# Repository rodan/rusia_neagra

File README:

power supply assy redesign for the Rusia Neagra MKII amplifier made by VIOTUBEAMP

https://www.tehnium-azi.ro/forums/topic/6689-proiectul-nr49-amplificatorul-rusia-neagra/?tab=comments#comment-73357

pictures of the build are available here:
https://photos.app.goo.gl/SxAB8hwyef6rpiTH7

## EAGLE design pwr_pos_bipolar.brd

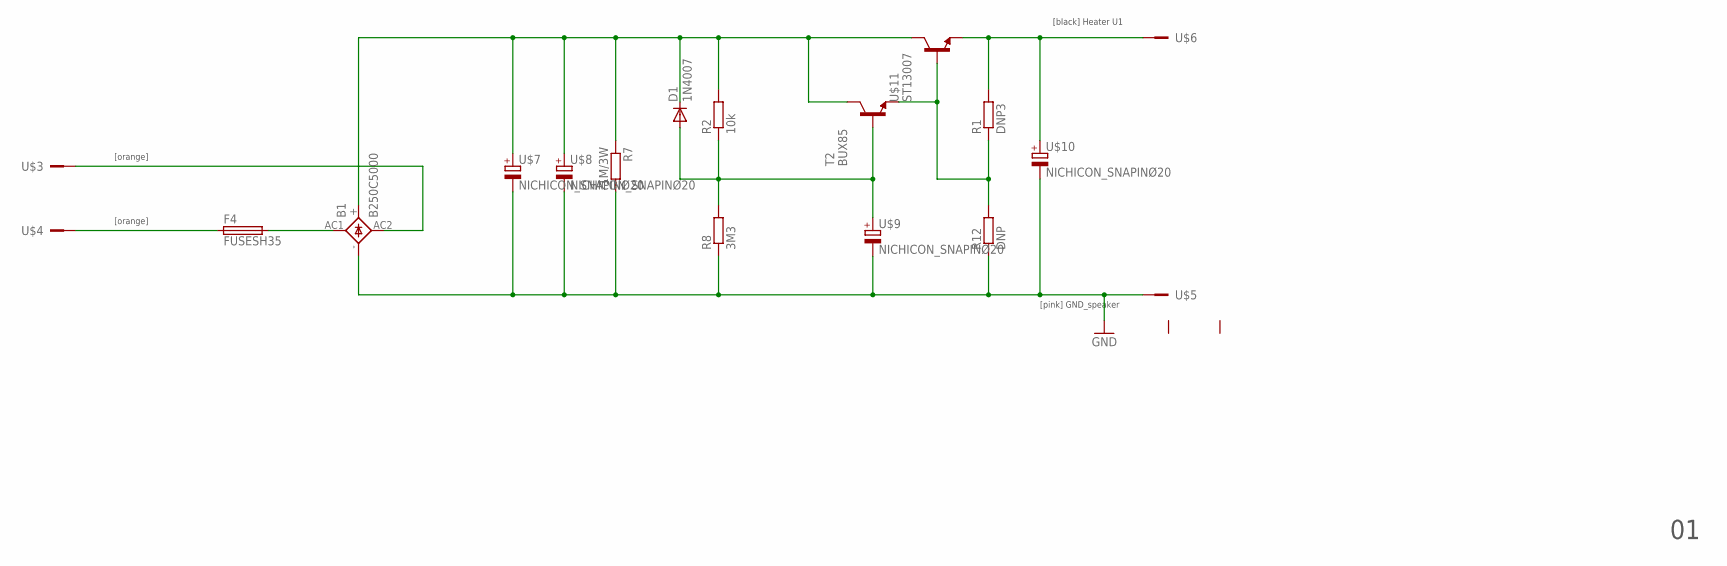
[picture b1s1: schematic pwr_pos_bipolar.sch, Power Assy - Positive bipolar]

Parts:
B1: B250C5000; DIOTEC_BC5000
D1: 1N4007; DO41-10
F4: FUSESH35; SH25
R1: DNP3; 0411/12
R2: 10k; 0411/12
R7: 1M/3W; 0922V
R8: 3M3; 0411/12
R12: DNP; 0411/12
T2: BUX85; TO220V
U$1: SK456-60-3XM3L
U$2: RN_POWER; RN
U$3, U$4, U$5, U$6: M1; M1_OFFSET
U$7, U$8, U$9, U$10: NICHICON_SNAPINØ20; C_20G10
U$11: ST13007; TOP3V_TO220

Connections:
30VAC_1: B1.AC2, U$3.1
30VAC_2: F4.1, U$4.1
GND: B1.-, R7.2, R8.1, R12.1, U$5.1, U$7.-, U$8.-, U$9.-, U$10.-
unnamed: B1.AC1, F4.2
unnamed: R1.1, R12.2, T2.3 (E), U$11.B, U$11.B$1 (B)
unnamed: D1.A, R2.1, R8.2, T2.1 (B), U$9.+
N_C: B1.+, D1.C, R2.2, R7.1, T2.2 (C), U$7.+, U$8.+, U$11.C
V-: R1.2, U$6.1, U$10.+, U$11.E, U$11.E$1 (E)

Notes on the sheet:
[orange]
[pink] GND_speaker
[black] Heater U1

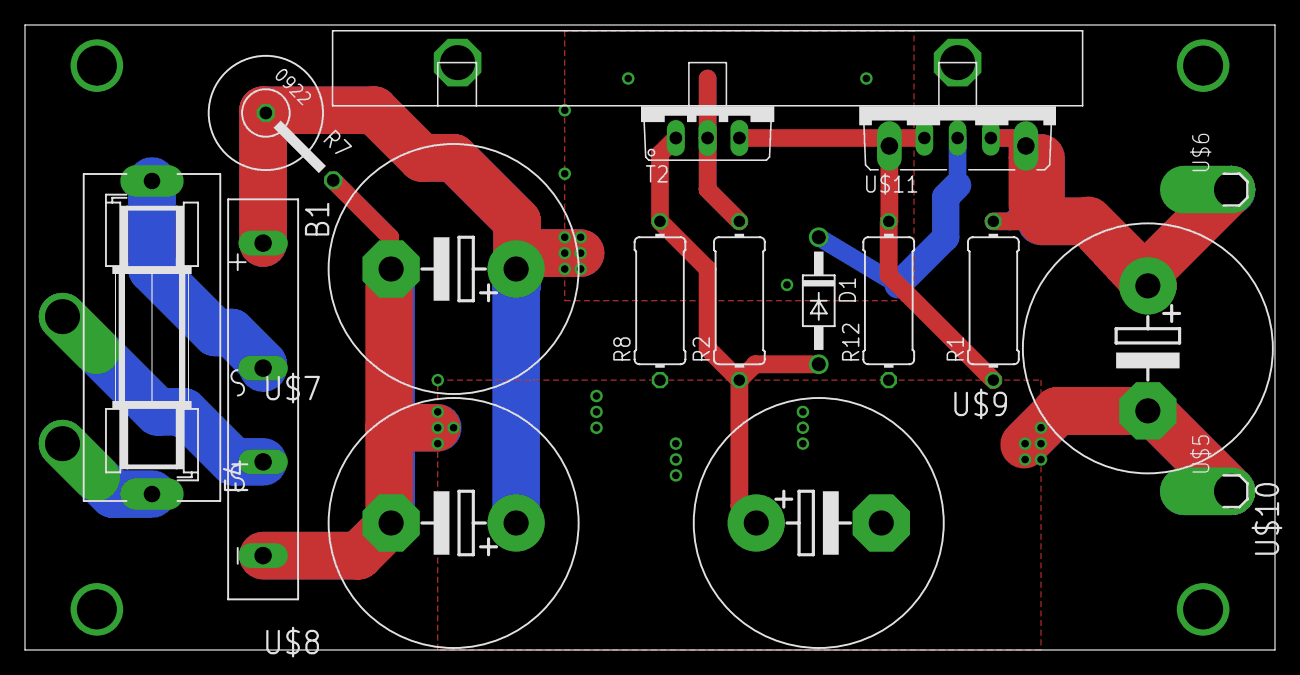
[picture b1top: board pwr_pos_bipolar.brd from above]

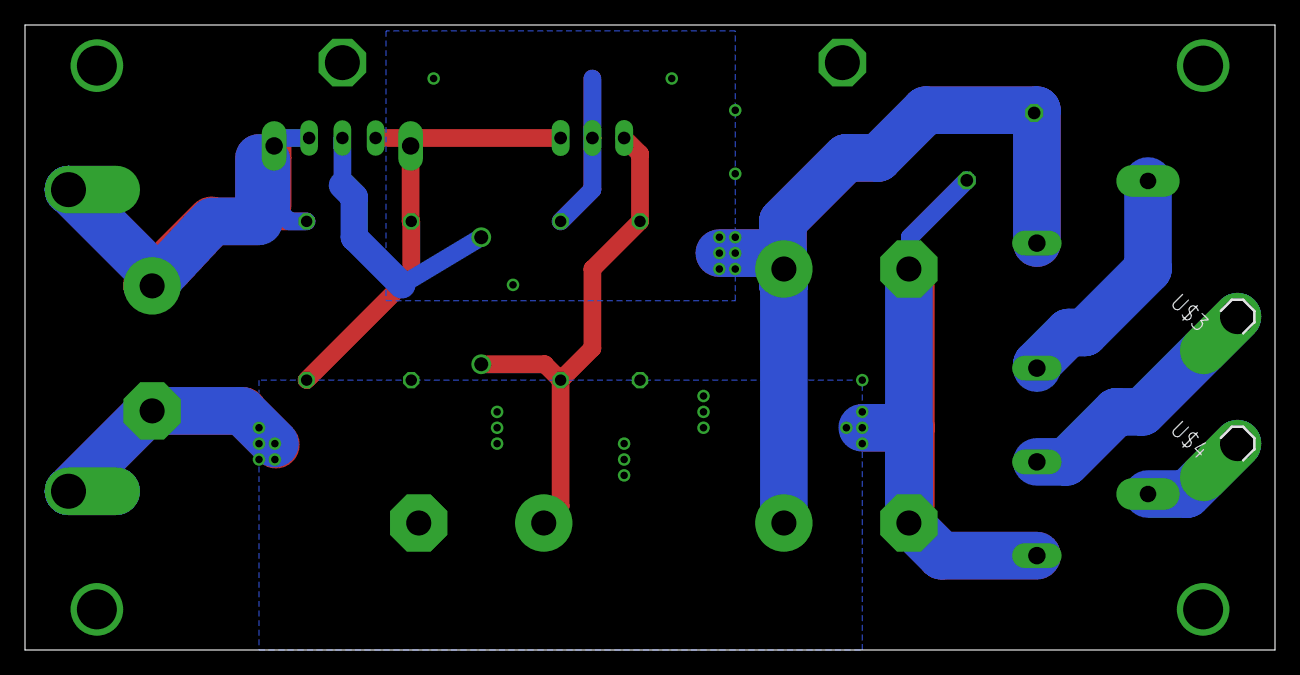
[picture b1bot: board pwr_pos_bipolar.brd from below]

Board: 2 copper layers, 100.0 x 50.0 mm, 20 parts (2 on the bottom side), 8 nets.

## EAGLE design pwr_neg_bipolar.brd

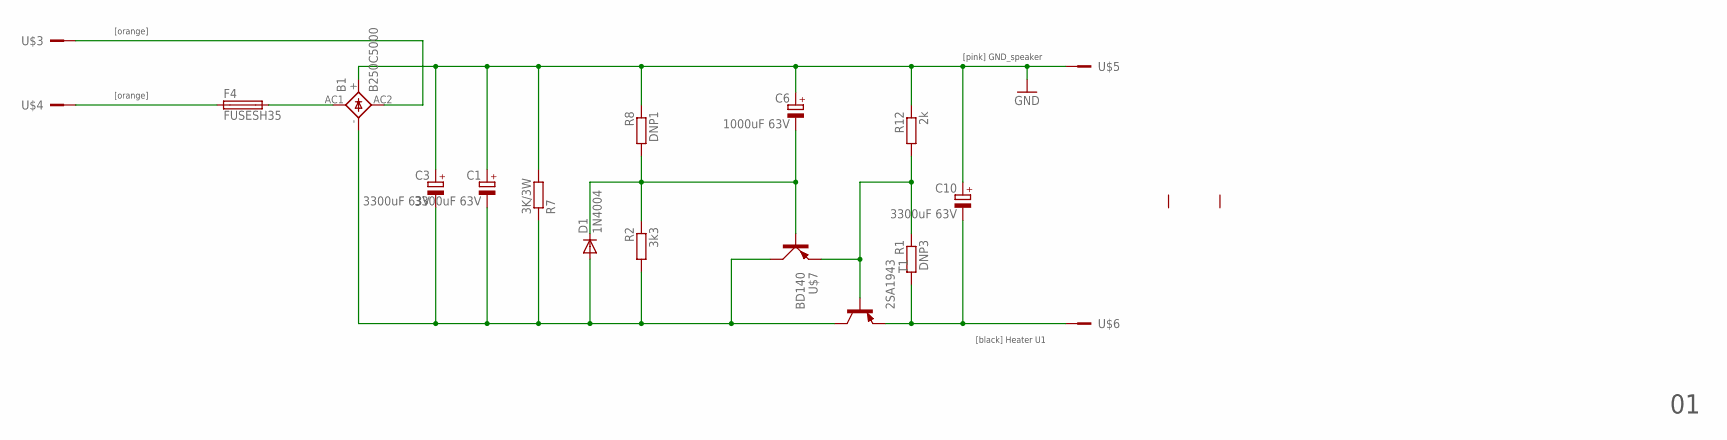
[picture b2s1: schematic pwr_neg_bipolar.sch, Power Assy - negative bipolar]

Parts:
B1: B250C5000; DIOTEC_BC5000
C1, C3, C10: 3300uF 63V; EB20D
C6: 1000uF 63V; E7,5-16
D1: 1N4004; DO41-10
F4: FUSESH35; SH25
R1: DNP3; 0411/12
R2: 3k3; 0411/12
R7: 3K/3W; 0922V
R8: DNP1; 0411/12
R12: 2k; 0411/12
T1: 2SA1943; TOP3V
U$1: SK456-60-3XM3L
U$2: RN_POWER; RN
U$3, U$4, U$5, U$6: M1; M1_OFFSET
U$7: BD140; SOT32

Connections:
30VAC_1: B1.AC2, U$3.1
30VAC_2: F4.1, U$4.1
GND: B1.+, C1.+, C3.+, C6.+, C10.+, R7.2, R8.1, R12.1, U$5.1
unnamed: B1.AC1, F4.2
unnamed: R1.1, R12.2, T1.B, U$7.E
unnamed: C6.-, D1.C, R2.1, R8.2, U$7.B
N_C: B1.-, C1.-, C3.-, D1.A, R2.2, R7.1, T1.C, U$7.C
V-: C10.-, R1.2, T1.E, U$6.1

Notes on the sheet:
[orange]
[pink] GND_speaker
[black] Heater U1

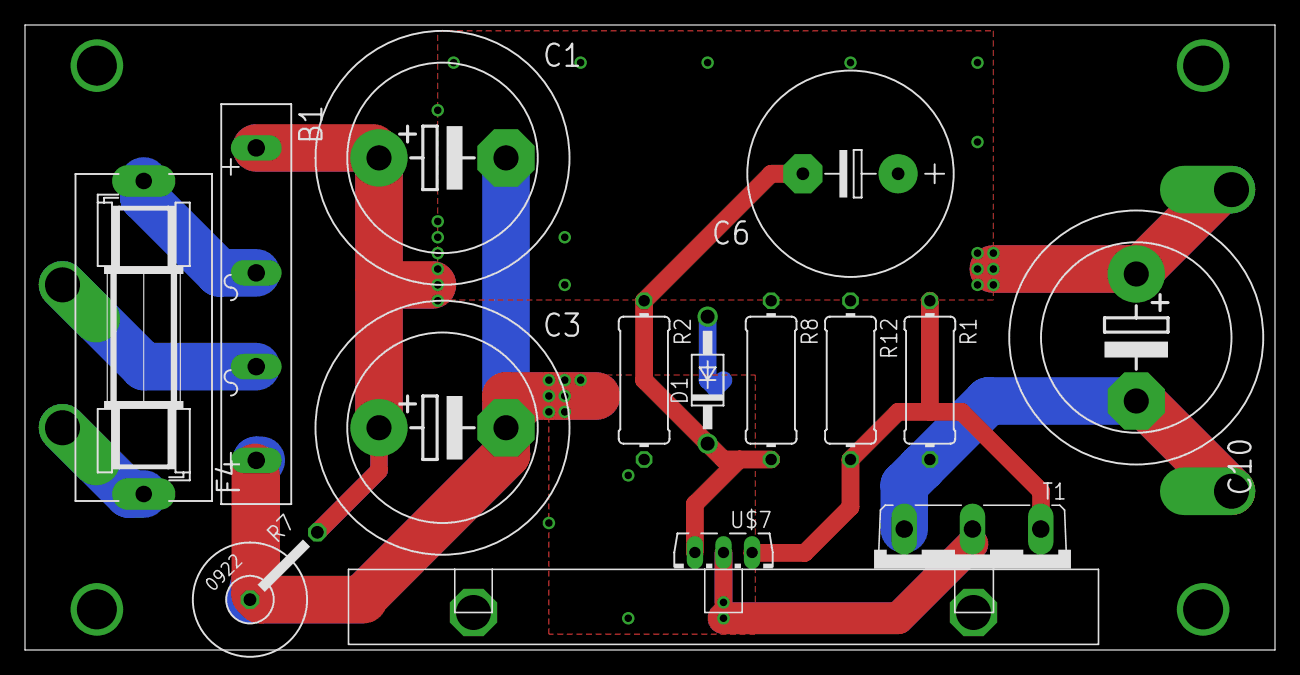
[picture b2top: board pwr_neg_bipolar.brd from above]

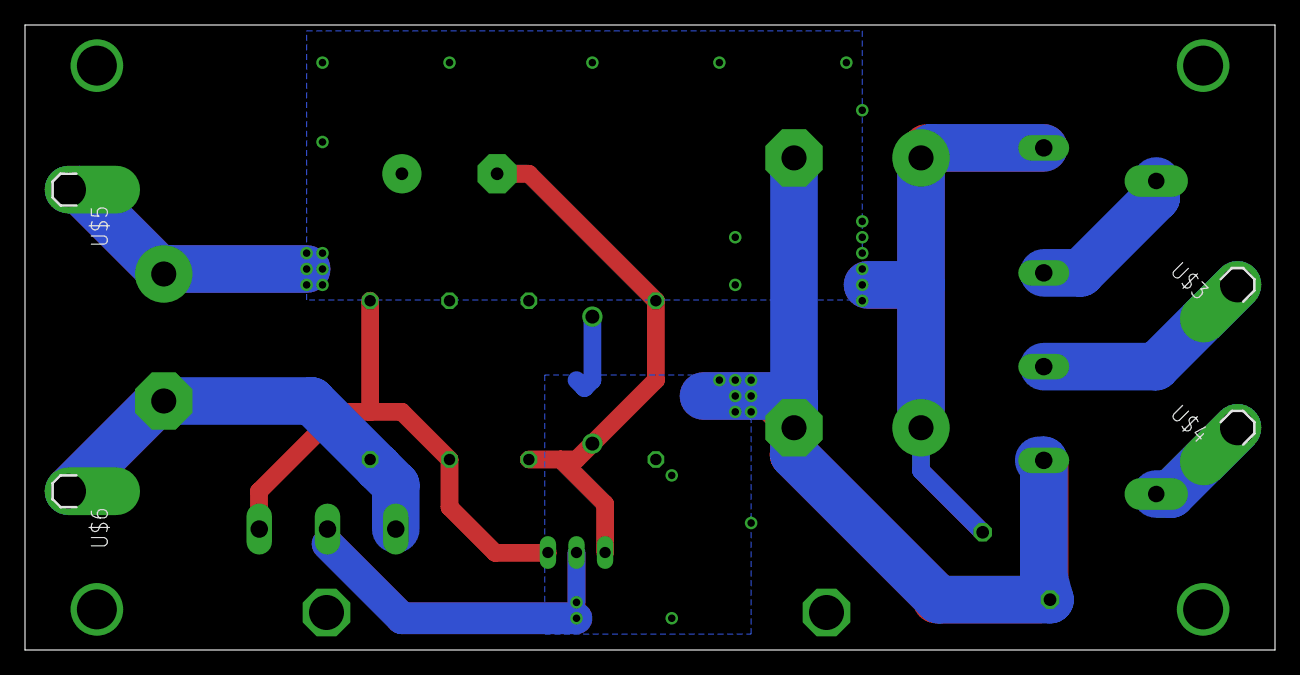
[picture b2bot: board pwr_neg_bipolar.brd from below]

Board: 2 copper layers, 100.0 x 50.0 mm, 20 parts (4 on the bottom side), 8 nets.

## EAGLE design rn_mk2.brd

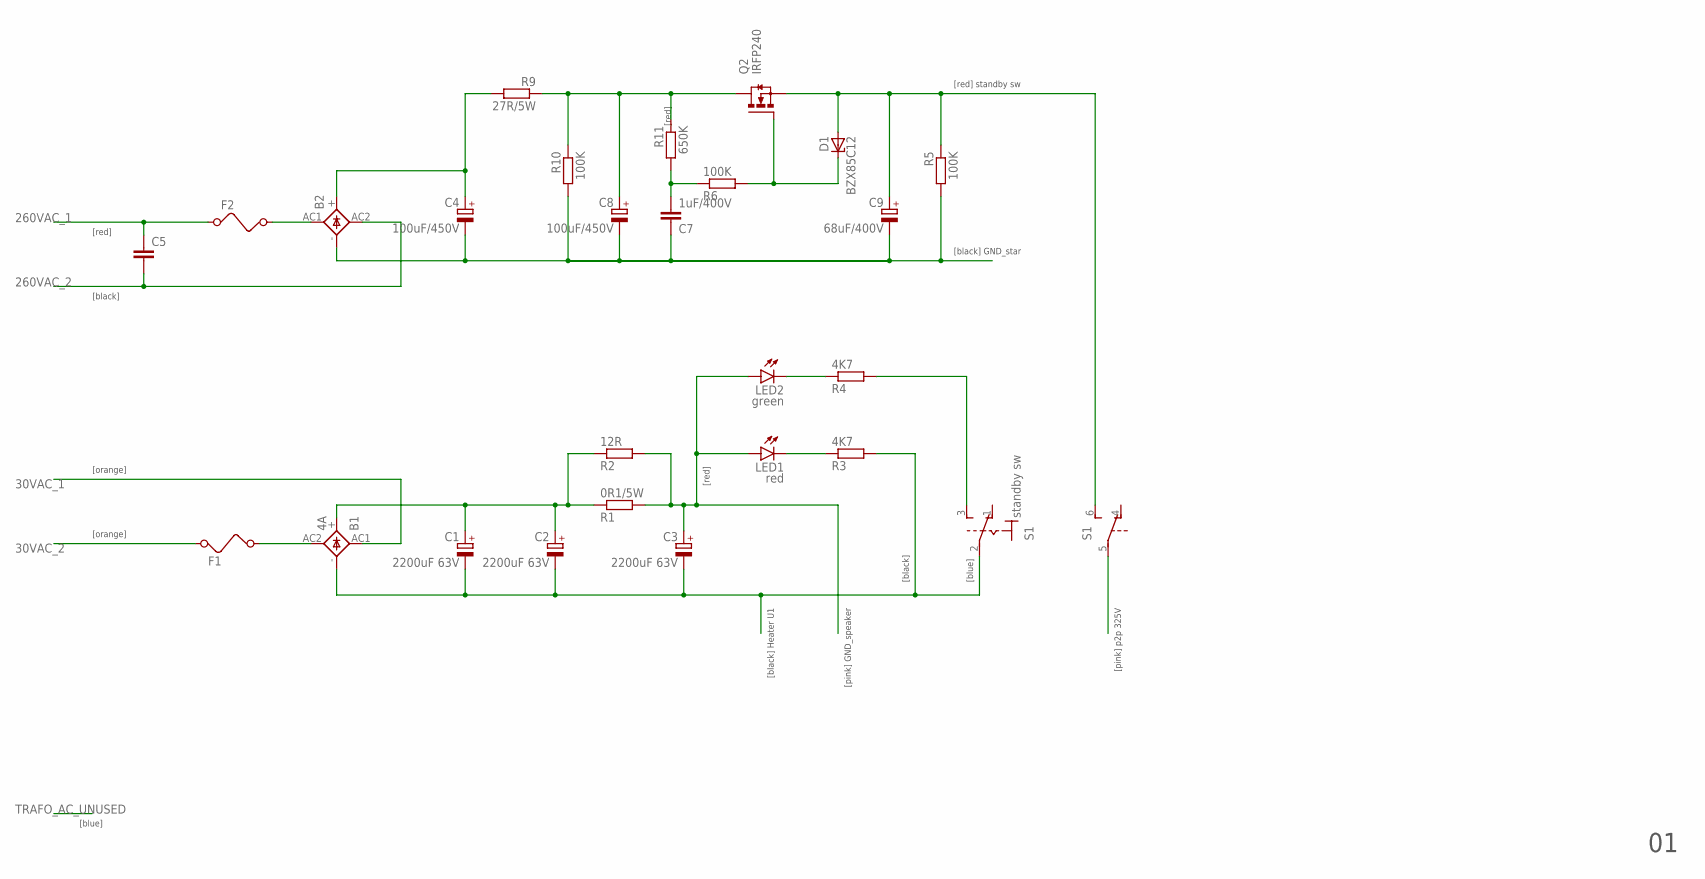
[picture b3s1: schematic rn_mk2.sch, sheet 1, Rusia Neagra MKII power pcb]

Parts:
B1: 4A; DIOTEC_BC5000
B2: DIOTEC_BC5000
C1, C2, C3: 2200uF 63V; E7,5-18
C4, C8: 100uF/450V; E7,5-18
C5: C-EU075-032X103; C075-032X103
C7: 1uF/400V; C075-032X103
C9: 68uF/400V; E7,5-18
D1: BZX85C12; DO41Z10
F1, F2: FUSE
LED1: red; LED3MM
LED2: green; LED3MM
Q2: IRFP240; TO247BV
R1: 0R1/5W; 0922/22
R2: 12R; 0922/22
R3, R4: 4K7; 0922/22
R5, R6, R10: 100K; 0922/22
R9: 27R/5W; 0922/22
R11: 650K; 0922/22
S1: standby sw; 320-938

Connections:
30VAC_1: B1.AC1
30VAC_2: F1.1
260VAC_1: C5.1, F2.1
260VAC_2: B2.AC2, C5.2
unnamed: B1.-, C1.-, C2.-, C3.-, R3.2, S1.2
unnamed: B1.AC2, F1.2
unnamed: B1.+, C1.+, C2.+, R1.1, R2.1
unnamed: C3.+, LED1.A, LED2.A, R1.2, R2.2
unnamed: LED1.K (C), R3.1
unnamed: LED2.K (C), R4.1
unnamed: R4.2, S1.3 (S)
unnamed: B2.AC1, F2.2
unnamed: B2.+, C4.+, R9.2
unnamed: B2.-, C4.-, C7.1, C8.-, C9.-, R5.2, R10.2
unnamed: C8.+, Q2.D, R9.1, R10.1, R11.1
unnamed: C7.2, R6.1, R11.2
unnamed: D1.C, Q2.G, R6.2
unnamed: C9.+, D1.A, Q2.S, R5.1, S1.6 (S)

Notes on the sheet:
[orange]
[pink] GND_speaker
[black] Heater U1
[red]
[blue]
[black]
[black] GND_star
[red] standby sw
[pink] p2p 325V

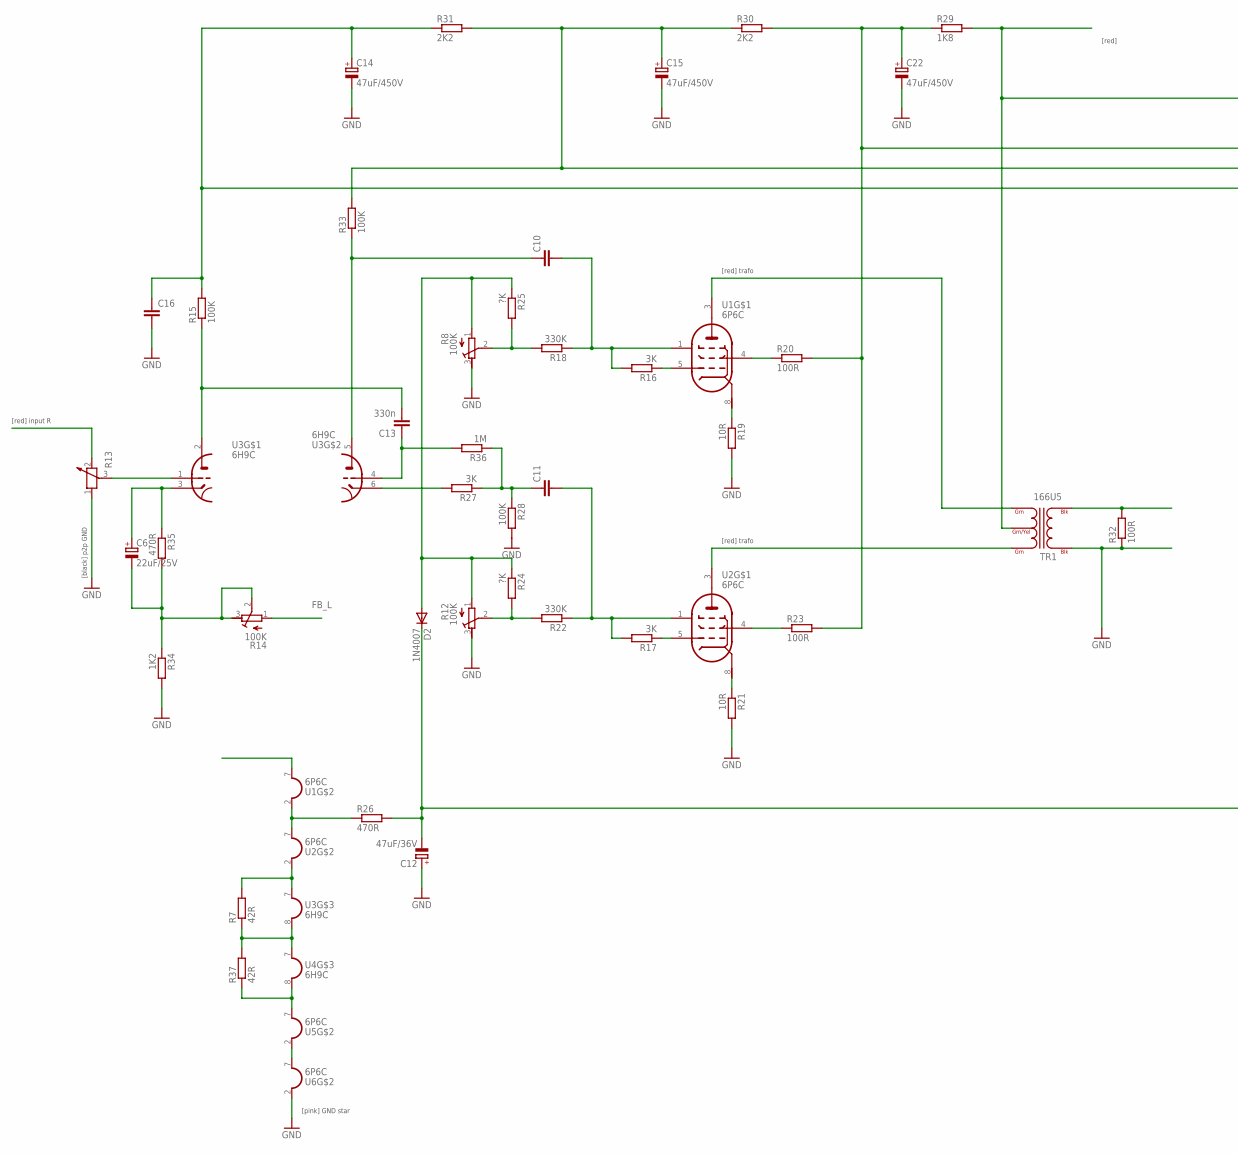
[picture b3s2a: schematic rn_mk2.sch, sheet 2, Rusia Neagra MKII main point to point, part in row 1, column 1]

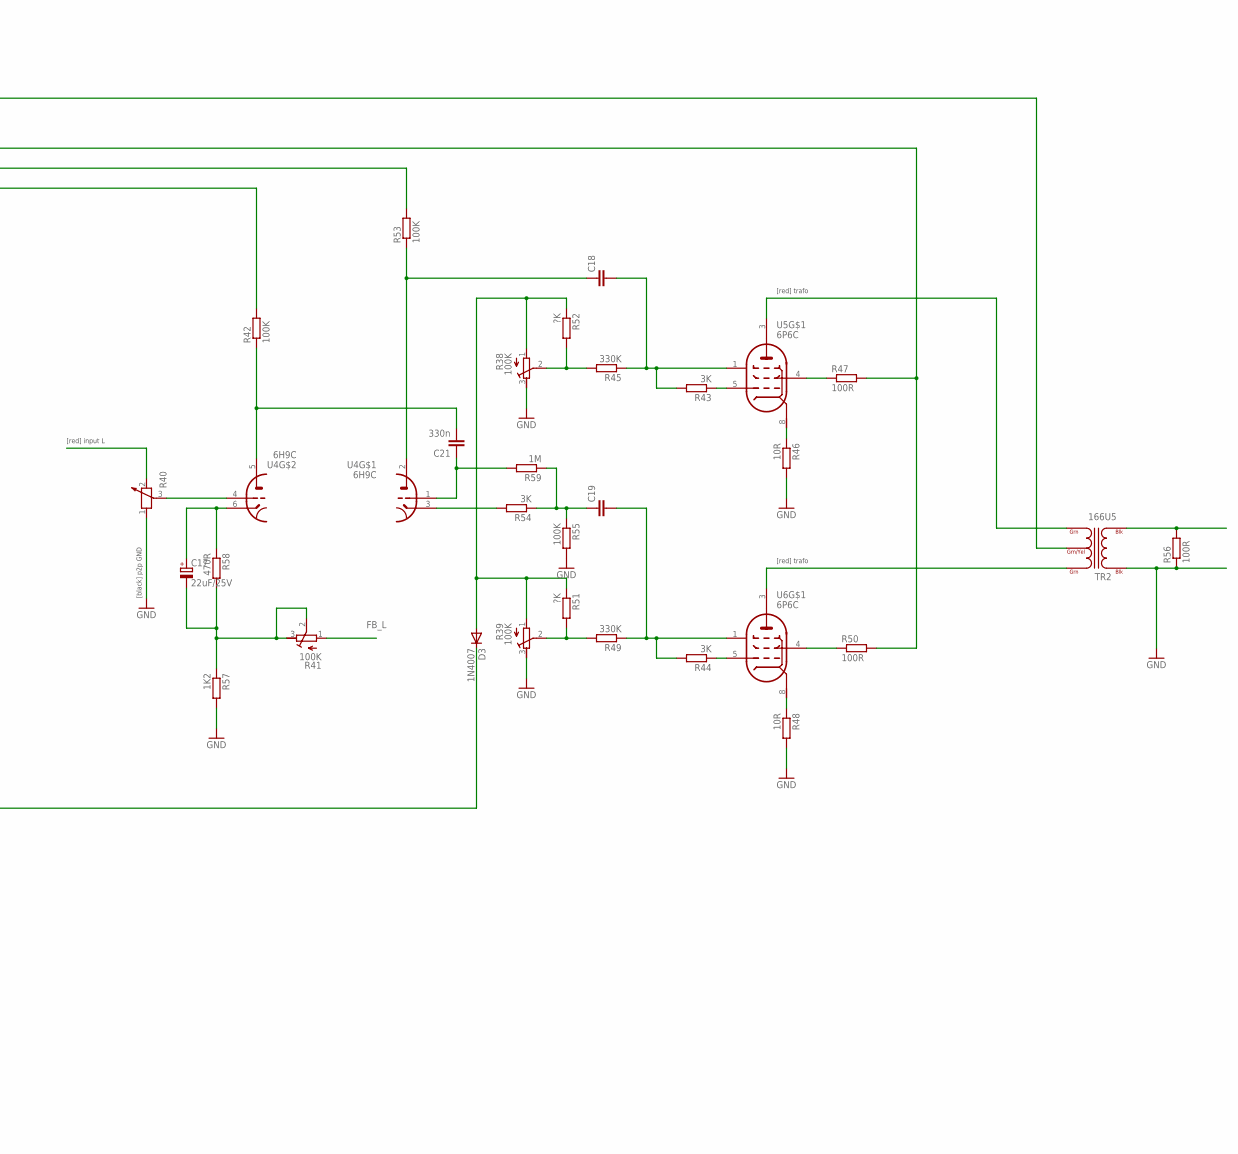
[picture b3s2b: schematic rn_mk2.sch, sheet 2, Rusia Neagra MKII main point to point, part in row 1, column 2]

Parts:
C6, C17: 22uF/25V; E5-5
C10, C11, C16, C18, C19: C-EU150-054X183; C150-054X183
C12: 47uF/36V; E5-5
C13, C21: 330n; C150-054X183
C14, C15, C22: 47uF/450V; E5-5
D2, D3: 1N4007; DO41-10
R7, R37: 42R; 0414/15
R8, R12, R14, R38, R39, R41: 100K; RTRIM64Y
R13, R40: POTENTIOMETER_PT-10; PT-10
R15, R28, R33, R42, R53, R55: 100K; 0414/15
R16, R17, R27, R43, R44, R54: 3K; 0414/15
R18, R22, R45, R49: 330K; 0414/15
R19, R21, R46, R48: 10R; 0414/15
R20, R23, R32, R47, R50, R56: 100R; 0414/15
R24, R25, R51, R52: ?K; 0414/15
R26: 470R; 0922/22
R29: 1K8; 0414/15
R30, R31: 2K2; 0414/15
R34, R57: 1K2; 0414/15
R35, R58: 470R; 0414/15
R36, R59: 1M; 0414/15
TR1, TR2: 166U5; C14H
U1, U2, U5, U6: 6P6C; OKTAL
U3, U4: 6H9C; OKTAL

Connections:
FB_L: R14.1 (A), R41.1 (A)
GND: C12.+, C14.-, C15.-, C16.2, C22.-, R8.3 (E), R12.3 (E), R13.1, R19.2, R21.2, R28.2, R32.1, R34.2, R38.3 (E), R39.3 (E), R40.1, R46.2, R48.2, R55.2, R56.1, R57.2, TR1.BLK@1 (BLK), TR2.BLK@1 (BLK), U6.2 (H1)
unnamed: R26.1, U1.2 (H1), U2.7 (H2)
unnamed: R7.2, U2.2 (H1), U3.7 (H1)
unnamed: R7.1, R37.2, U3.8 (H2), U4.7 (H1)
unnamed: R13.3, U3.1 (TG1)
unnamed: R16.1, U1.5 (PG)
unnamed: C13.2, R15.1, U3.2 (TA1)
unnamed: C6.+, R35.1, U3.3 (T1)
unnamed: C13.1, R36.2, U3.4 (TG2)
unnamed: C10.2, R16.2, R18.1, U1.1 (SH)
unnamed: R17.1, U2.5 (PG)
unnamed: C11.2, R17.2, R22.1, U2.1 (SH)
unnamed: C10.1, R33.1, U3.5 (TA2)
unnamed: TR1.GRN@2 (GRN), U1.3 (PA)
unnamed: R8.2 (S), R18.2, R25.2
unnamed: R19.1, U1.8 (PK)
unnamed: R20.1, U1.4 (PSG)
unnamed: D2.A, R8.1 (A), R12.1 (A), R24.1, R25.1
unnamed: TR1.GRN@1 (GRN), U2.3 (PA)
unnamed: R21.1, U2.8 (PK)
unnamed: R12.2 (S), R22.2, R24.2
unnamed: C12.-, D2.C, D3.C, R26.2
unnamed: R23.1, U2.4 (PSG)
unnamed: R40.3, U4.4 (TG2)
unnamed: C11.1, R27.1, R28.1, R36.1
unnamed: R27.2, U3.6 (T2)
unnamed: C15.+, R30.1, R31.2, R33.2, R53.2
unnamed: U5.2 (H1), U6.7 (H2)
unnamed: C22.+, R20.2, R23.2, R29.1, R30.2, R47.2, R50.2
unnamed: C6.-, R14.2 (S), R14.3 (E), R34.1, R35.2
unnamed: C14.+, C16.1, R15.2, R31.1, R42.2
unnamed: R32.2, TR1.BLK@2 (BLK)
unnamed: R37.1, U4.8 (H2), U5.7 (H2)
unnamed: R54.2, U4.3 (T1)
unnamed: C21.2, R42.1, U4.5 (TA2)
unnamed: C17.+, R58.1, U4.6 (T2)
unnamed: R43.1, U5.5 (PG)
unnamed: C18.2, R43.2, R45.1, U5.1 (SH)
unnamed: R44.1, U6.5 (PG)
unnamed: C19.2, R44.2, R49.1, U6.1 (SH)
unnamed: C18.1, R53.1, U4.2 (TA1)
unnamed: R46.1, U5.8 (PK)
unnamed: R47.1, U5.4 (PSG)
unnamed: D3.A, R38.1 (A), R39.1 (A), R51.1, R52.1
unnamed: R48.1, U6.8 (PK)
unnamed: R39.2 (S), R49.2, R51.2
unnamed: R50.1, U6.4 (PSG)
unnamed: R29.2, TR1.GRN/YEL, TR2.GRN/YEL
unnamed: R38.2 (S), R45.2, R52.2
unnamed: TR2.GRN@1 (GRN), U6.3 (PA)
unnamed: TR2.GRN@2 (GRN), U5.3 (PA)
unnamed: C19.1, R54.1, R55.1, R59.1
unnamed: R56.2, TR2.BLK@2 (BLK)
unnamed: C17.-, R41.2 (S), R41.3 (E), R57.1, R58.2
unnamed: C21.1, R59.2, U4.1 (TG1)

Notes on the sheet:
[black] p2p GND
[red] input R
[red] trafo
[red]
[red] input L
[pink] GND star

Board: 2 copper layers, 99 parts (6 on the bottom side), 72 nets, no tracks yet.

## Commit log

2020-04-19 ripple filter built and tested
2020-04-26 latest
2020-04-26 add libraries
2020-05-01 build done
2020-06-05 remove local pictures

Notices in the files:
parts and their libraries:
SparkFun-LED: Licensing: Creative Commons ShareAlike 4.0 International - https://creativecommons.org/licenses/by-sa/4.0
